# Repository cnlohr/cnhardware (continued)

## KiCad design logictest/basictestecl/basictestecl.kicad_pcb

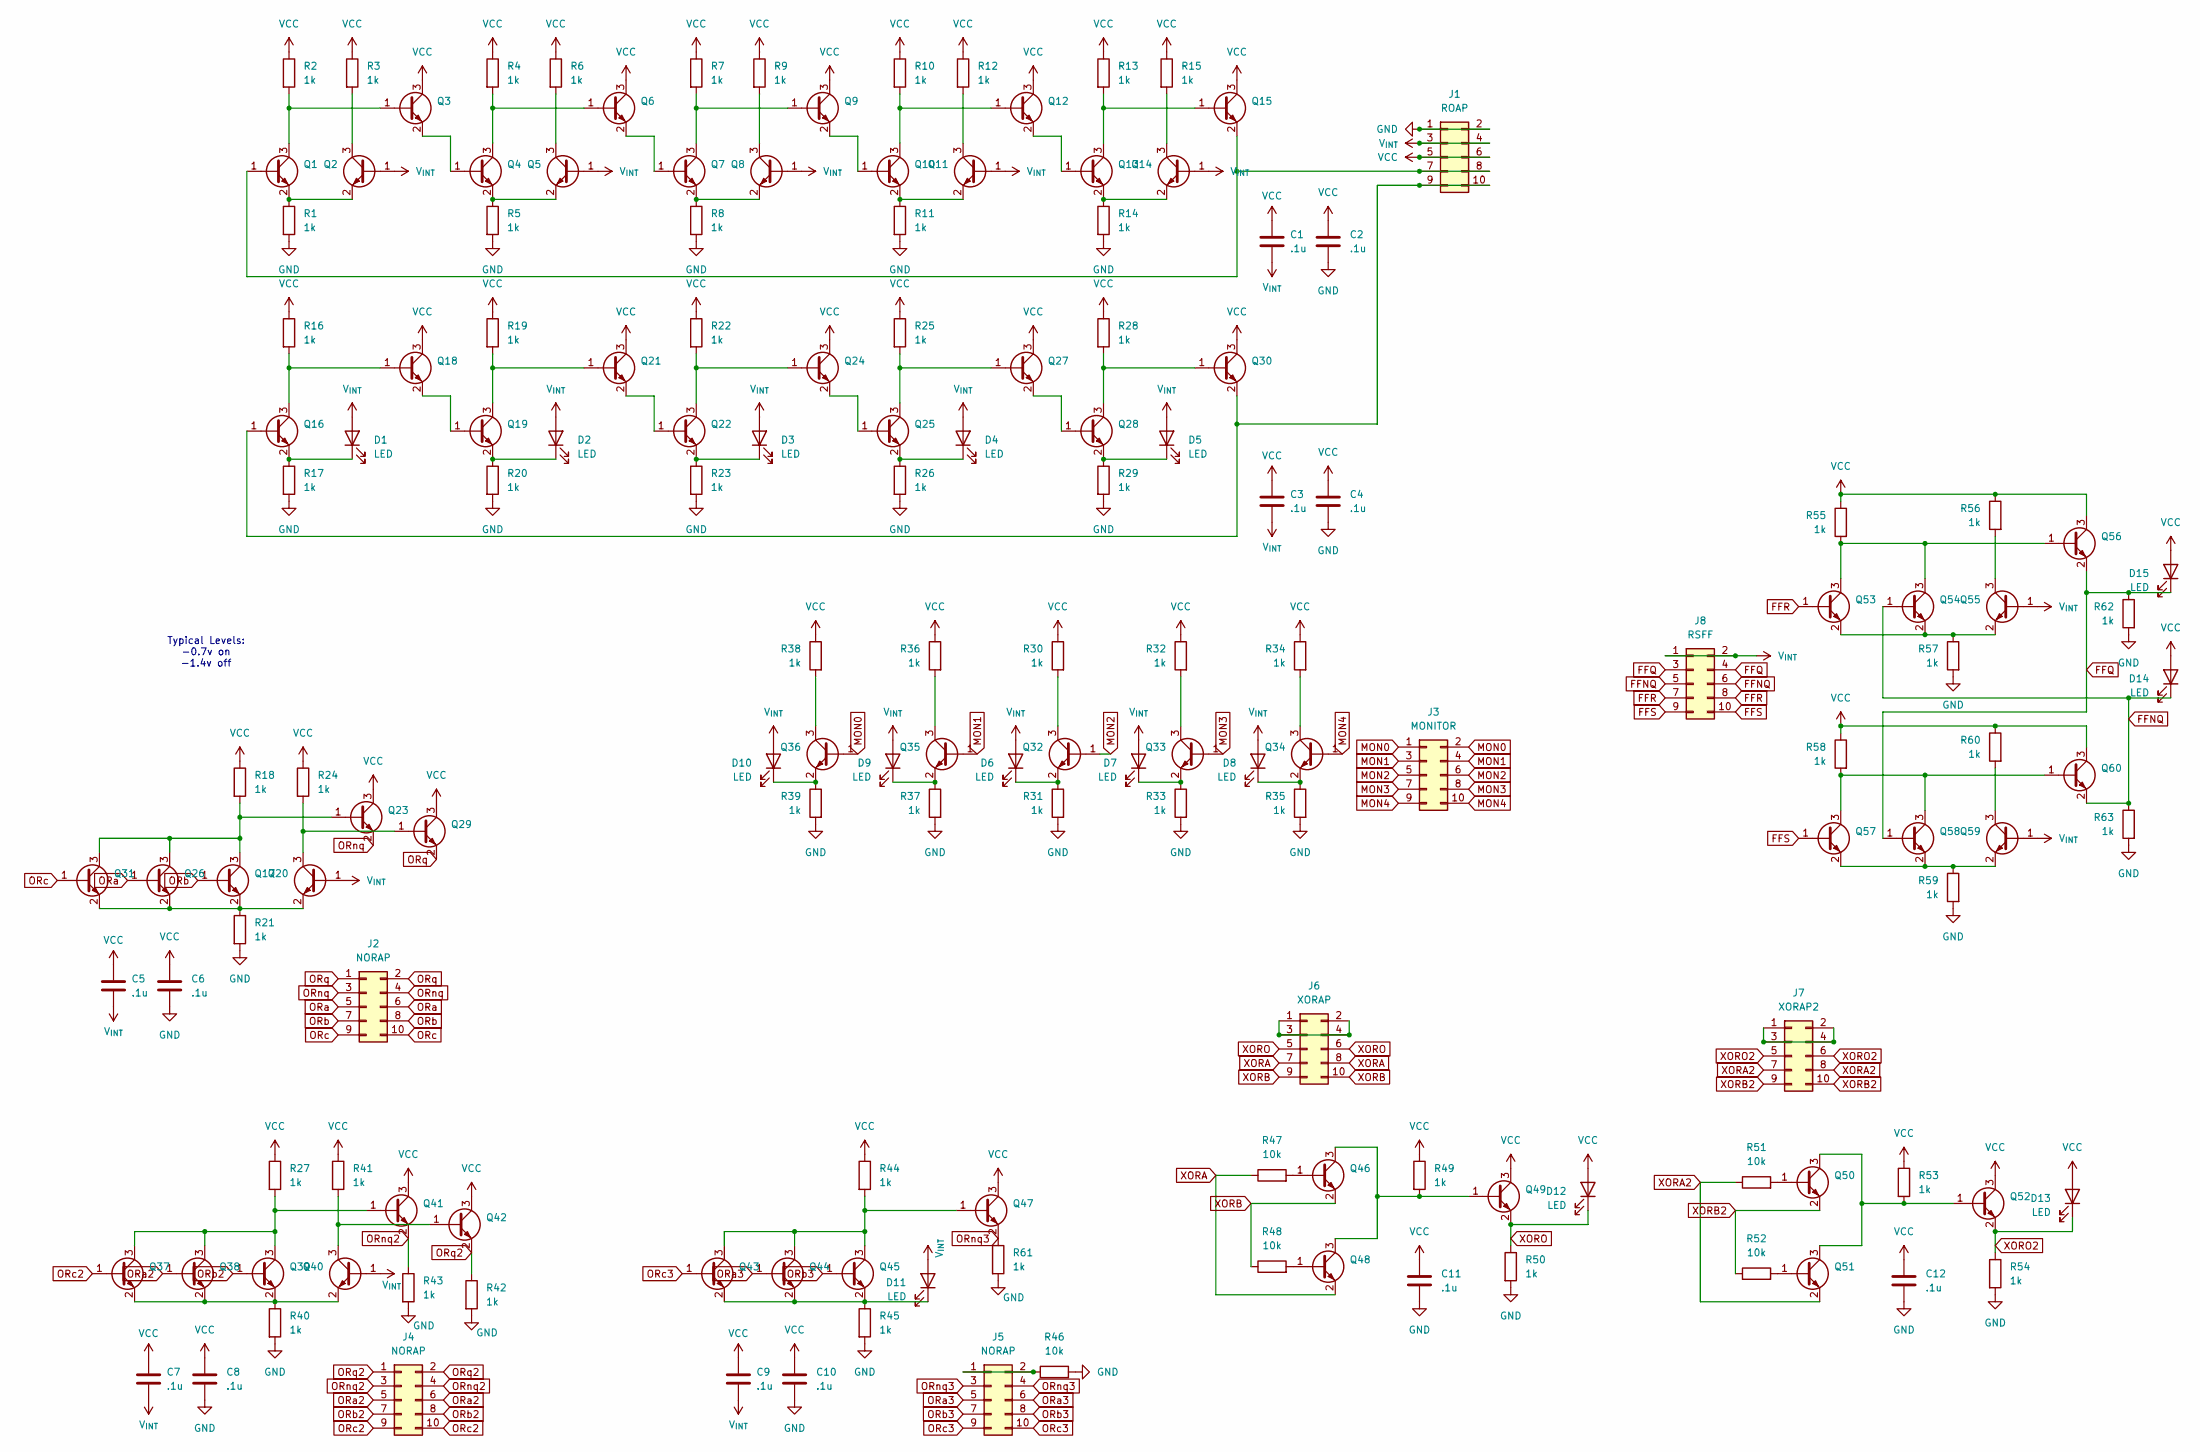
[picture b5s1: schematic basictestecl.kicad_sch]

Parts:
C1, C2, C3, C4, C5, C6, C7, C8, C9, C10, C11, C12: .1u; C_0402_1005Metric; LCSC C1525
D1, D2, D3, D4, D5, D6, D7, D8, D9, D10, D11, D12, D13, D14, D15: LED; LED_0402_1005Metric_COMPACT; LCSC C52675960
J1: ROAP; PinHeader_2x05_P2.54mm_Vertical; LCSC C53055680
J2, J4, J5: NORAP; PinHeader_2x05_P2.54mm_Vertical; LCSC C53055680
J3: MONITOR; PinHeader_2x05_P2.54mm_Vertical; LCSC C53055680
J6: XORAP; PinHeader_2x05_P2.54mm_Vertical; LCSC C53055680
J7: XORAP2; PinHeader_2x05_P2.54mm_Vertical; LCSC C53055680
J8: RSFF; PinHeader_2x05_P2.54mm_Vertical; LCSC C53055680
Q1, Q2, Q3, Q4, Q5, Q6, Q7, Q8, Q9, Q10, Q11, Q12, Q13, Q14, Q15, Q16, Q17, Q18, Q19, Q20, Q21, Q22, Q23, Q24, Q25, Q26, Q27, Q28, Q29, Q30, Q31, Q32, Q33, Q34, Q35, Q36, Q37, Q38, Q39, Q40, Q41, Q42, Q43, Q44, Q45, Q46, Q47, Q48, Q49, Q50, Q51, Q52, Q53, Q54, Q55, Q56, Q57, Q58, Q59, Q60: Q_NPN_BEC; DFN1006-3-NCH; LCSC C41355105
R1, R2, R3, R4, R5, R6, R7, R8, R9, R10, R11, R12, R13, R14, R15, R16, R17, R18, R19, R20, R21, R22, R23, R24, R25, R26, R27, R28, R29, R30, R31, R32, R33, R34, R35, R36, R37, R38, R39, R40, R41, R42, R43, R44, R45, R49, R50, R53, R54, R55, R56, R57, R58, R59, R60, R61, R62, R63: 1k; R_0402_1005Metric_COMPACT; LCSC C11702
R46, R47, R48, R51, R52: 10k; R_0402_1005Metric_COMPACT; LCSC C25744

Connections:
FFNQ: D14.1 (K), J8.5, J8.6, Q54.1 (B), Q60.2 (E), R63.1
FFQ: D15.1 (K), J8.3, J8.4, Q56.2 (E), Q58.1 (B), R62.1
FFR: J8.7, J8.8, Q53.1 (B)
FFS: J8.9, J8.10, Q57.1 (B)
GND: C2.2, C4.2, C6.2, C8.2, C10.2, C11.2, C12.2, J1.1, J1.2, R1.2, R5.2, R8.2, R11.2, R14.2, R17.2, R20.2, R21.2, R23.2, R26.2, R29.2, R31.2, R33.2, R35.2, R37.2, R39.2, R40.2, R42.2, R43.2, R45.2, R46.2, R50.2, R54.2, R57.2, R59.2, R61.2, R62.2, R63.2
MON0: J3.1, J3.2, Q36.1 (B)
MON1: J3.3, J3.4, Q35.1 (B)
MON2: J3.5, J3.6, Q32.1 (B)
MON3: J3.7, J3.8, Q33.1 (B)
MON4: J3.9, J3.10, Q34.1 (B)
unnamed: D1.1 (K), Q16.2 (E), R17.1
unnamed: D2.1 (K), Q19.2 (E), R20.1
unnamed: D3.1 (K), Q22.2 (E), R23.1
unnamed: D4.1 (K), Q25.2 (E), R26.1
unnamed: D5.1 (K), Q28.2 (E), R29.1
unnamed: D6.1 (K), Q32.2 (E), R31.1
unnamed: D7.1 (K), Q33.2 (E), R33.1
unnamed: D8.1 (K), Q34.2 (E), R35.1
unnamed: D9.1 (K), Q35.2 (E), R37.1
unnamed: D10.1 (K), Q36.2 (E), R39.1
unnamed: D11.1 (K), Q43.2 (E), Q44.2 (E), Q45.2 (E), R45.1
unnamed: J1.7, J1.8, Q1.1 (B), Q15.2 (E)
unnamed: J1.9, J1.10, Q16.1 (B), Q30.2 (E)
unnamed: J5.1, J5.2, R46.1
unnamed: J6.1, J6.2, J6.3, J6.4
unnamed: J7.1, J7.2, J7.3, J7.4
unnamed: Q1.3 (C), Q3.1 (B), R2.2
unnamed: Q1.2 (E), Q2.2 (E), R1.1
unnamed: Q2.3 (C), R3.2
unnamed: Q3.2 (E), Q4.1 (B)
unnamed: Q4.3 (C), Q6.1 (B), R4.2
unnamed: Q4.2 (E), Q5.2 (E), R5.1
unnamed: Q5.3 (C), R6.2
unnamed: Q6.2 (E), Q7.1 (B)
unnamed: Q7.3 (C), Q9.1 (B), R7.2
unnamed: Q7.2 (E), Q8.2 (E), R8.1
unnamed: Q8.3 (C), R9.2
unnamed: Q9.2 (E), Q10.1 (B)
unnamed: Q10.3 (C), Q12.1 (B), R10.2
unnamed: Q10.2 (E), Q11.2 (E), R11.1
unnamed: Q11.3 (C), R12.2
unnamed: Q12.2 (E), Q13.1 (B)
unnamed: Q13.3 (C), Q15.1 (B), R13.2
unnamed: Q13.2 (E), Q14.2 (E), R14.1
unnamed: Q14.3 (C), R15.2
unnamed: Q16.3 (C), Q18.1 (B), R16.2
unnamed: Q17.3 (C), Q23.1 (B), Q26.3 (C), Q31.3 (C), R18.2
unnamed: Q17.2 (E), Q20.2 (E), Q26.2 (E), Q31.2 (E), R21.1
unnamed: Q18.2 (E), Q19.1 (B)
unnamed: Q19.3 (C), Q21.1 (B), R19.2
unnamed: Q20.3 (C), Q29.1 (B), R24.2
unnamed: Q21.2 (E), Q22.1 (B)
unnamed: Q22.3 (C), Q24.1 (B), R22.2
unnamed: Q24.2 (E), Q25.1 (B)
unnamed: Q25.3 (C), Q27.1 (B), R25.2
unnamed: Q27.2 (E), Q28.1 (B)
unnamed: Q28.3 (C), Q30.1 (B), R28.2
unnamed: Q32.3 (C), R30.2
unnamed: Q33.3 (C), R32.2
unnamed: Q34.3 (C), R34.2
unnamed: Q35.3 (C), R36.2
unnamed: Q36.3 (C), R38.2
unnamed: Q37.3 (C), Q38.3 (C), Q39.3 (C), Q41.1 (B), R27.2
unnamed: Q37.2 (E), Q38.2 (E), Q39.2 (E), Q40.2 (E), R40.1
unnamed: Q40.3 (C), Q42.1 (B), R41.2
unnamed: Q43.3 (C), Q44.3 (C), Q45.3 (C), Q47.1 (B), R44.2
unnamed: Q46.1 (B), R47.2
unnamed: Q46.3 (C), Q48.3 (C), Q49.1 (B), R49.2
unnamed: Q48.1 (B), R48.2
unnamed: Q50.1 (B), R51.2
unnamed: Q50.3 (C), Q51.3 (C), Q52.1 (B), R53.2
unnamed: Q51.1 (B), R52.2
unnamed: Q53.3 (C), Q54.3 (C), Q56.1 (B), R55.2
unnamed: Q53.2 (E), Q54.2 (E), Q55.2 (E), R57.1
unnamed: Q55.3 (C), R56.2
unnamed: Q57.3 (C), Q58.3 (C), Q60.1 (B), R58.2
unnamed: Q57.2 (E), Q58.2 (E), Q59.2 (E), R59.1
unnamed: Q59.3 (C), R60.2
ORa: J2.5, J2.6, Q26.1 (B)
ORa2: J4.5, J4.6, Q38.1 (B)
ORa3: J5.5, J5.6, Q44.1 (B)
ORb: J2.7, J2.8, Q17.1 (B)
ORb2: J4.7, J4.8, Q39.1 (B)
ORb3: J5.7, J5.8, Q45.1 (B)
ORc: J2.9, J2.10, Q31.1 (B)
ORc2: J4.9, J4.10, Q37.1 (B)
ORc3: J5.9, J5.10, Q43.1 (B)
ORnq: J2.3, J2.4, Q23.2 (E)
ORnq2: J4.3, J4.4, Q41.2 (E), R43.1
ORnq3: J5.3, J5.4, Q47.2 (E), R61.1
ORq: J2.1, J2.2, Q29.2 (E)
ORq2: J4.1, J4.2, Q42.2 (E), R42.1
VCC: C1.2, C2.1, C3.2, C4.1, C5.2, C6.1, C7.2, C8.1, C9.2, C10.1, C11.1, C12.1, D12.2 (A), D13.2 (A), D14.2 (A), D15.2 (A), J1.5, J1.6, Q3.3 (C), Q6.3 (C), Q9.3 (C), Q12.3 (C), Q15.3 (C), Q18.3 (C), Q21.3 (C), Q23.3 (C), Q24.3 (C), Q27.3 (C), Q29.3 (C), Q30.3 (C), Q41.3 (C), Q42.3 (C), Q47.3 (C), Q49.3 (C), Q52.3 (C), Q56.3 (C), Q60.3 (C), R2.1, R3.1, R4.1, R6.1, R7.1, R9.1, R10.1, R12.1, R13.1, R15.1, R16.1, R18.1, R19.1, R22.1, R24.1, R25.1, R27.1, R28.1, R30.1, R32.1, R34.1, R36.1, R38.1, R41.1, R44.1, R49.1, R53.1, R55.1, R56.1, R58.1, R60.1
V_{INT}: C1.1, C3.1, C5.1, C7.1, C9.1, D1.2 (A), D2.2 (A), D3.2 (A), D4.2 (A), D5.2 (A), D6.2 (A), D7.2 (A), D8.2 (A), D9.2 (A), D10.2 (A), D11.2 (A), J1.3, J1.4, J8.1, J8.2, Q2.1 (B), Q5.1 (B), Q8.1 (B), Q11.1 (B), Q14.1 (B), Q20.1 (B), Q40.1 (B), Q55.1 (B), Q59.1 (B)
XORA: J6.7, J6.8, Q48.2 (E), R47.1
XORA2: J7.7, J7.8, Q51.2 (E), R51.1
XORB: J6.9, J6.10, Q46.2 (E), R48.1
XORB2: J7.9, J7.10, Q50.2 (E), R52.1
XORO: D12.1 (K), J6.5, J6.6, Q49.2 (E), R50.1
XORO2: D13.1 (K), J7.5, J7.6, Q52.2 (E), R54.1

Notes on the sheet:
Typical Levels: -0.7v on -1.4v off

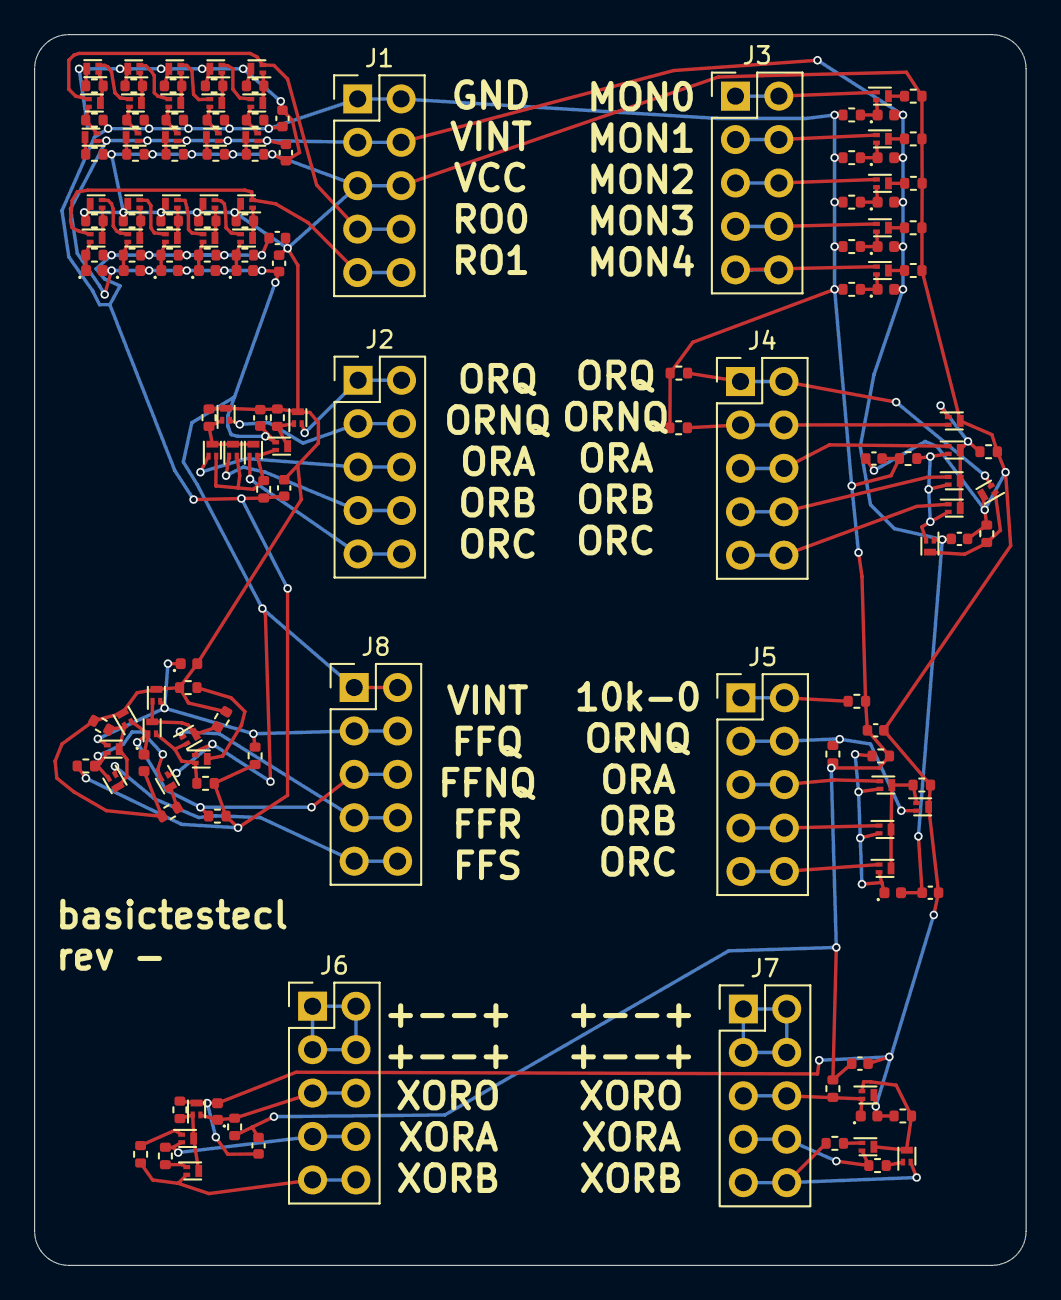
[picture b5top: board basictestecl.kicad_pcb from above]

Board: 2 copper layers, 58.0 x 72.0 mm, 158 parts (0 on the bottom side), 100 nets.

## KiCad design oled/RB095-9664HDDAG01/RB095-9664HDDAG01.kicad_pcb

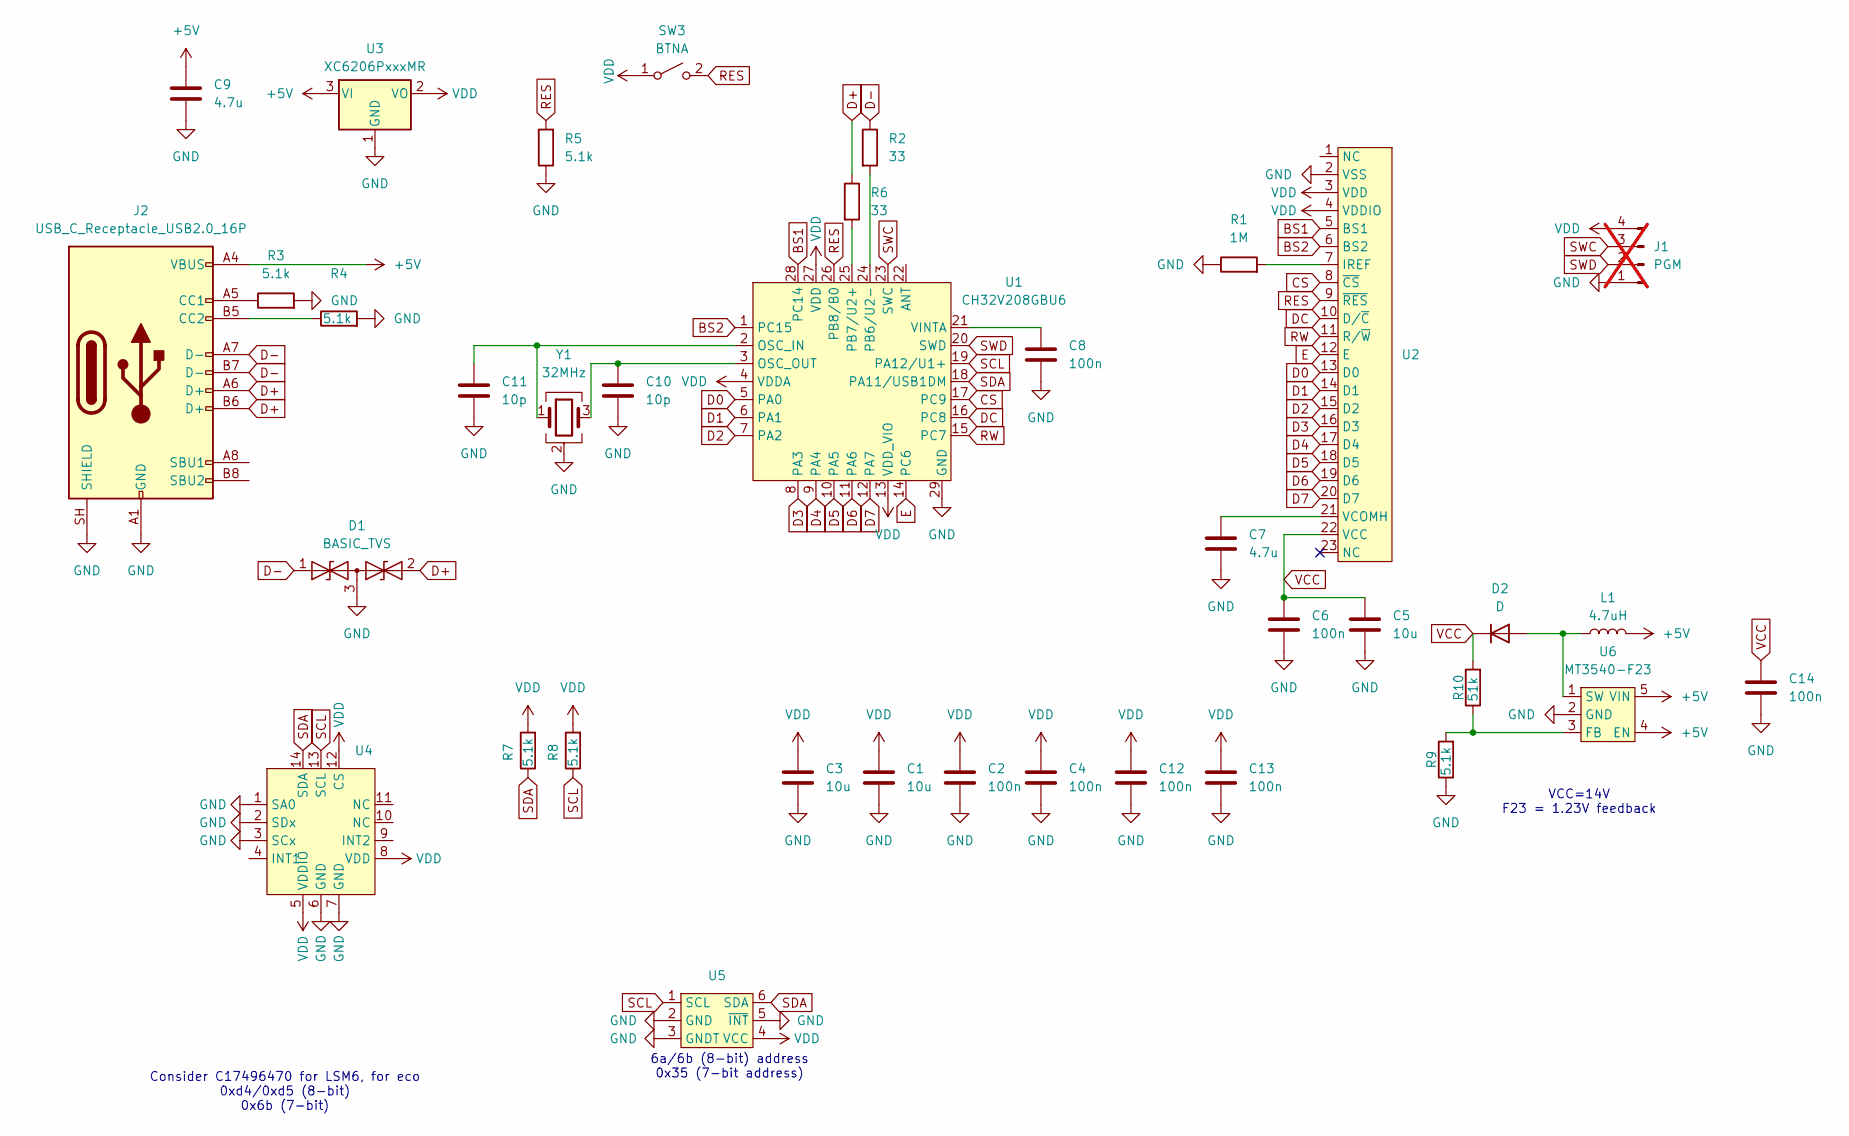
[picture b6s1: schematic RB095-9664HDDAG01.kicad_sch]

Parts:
C1, C3, C5: 10u; C_1206_3216Metric; LCSC C13585
C2, C4, C6, C8, C12, C13, C14: 100n; C_0402_1005Metric; LCSC C1525
C7, C9: 4.7u; C_1206_3216Metric; LCSC C29823
C10, C11: 10p; C_0402_1005Metric; LCSC C32949
D1: BASIC_TVS; SOT-23; LCSC C32677
D2: D; D_SOD-323; LCSC C191023
J1: PGM; PinHeader_1x04_P2.54mm_Vertical; not fitted
J2: USB_C_Receptacle_USB2.0_16P; USB_C_TIGHT_IN_BOARD_161N-4BC21665; LCSC C23376537
L1: 4.7uH; L_0805_2012Metric; LCSC C86088
R1: 1M; R_0402_1005Metric; LCSC C43675
R2, R6: 33; R_0402_1005Metric; LCSC C25105
R3, R4, R5, R7, R8, R9: 5.1k; R_0402_1005Metric; LCSC C25905
R10: 51k; R_0402_1005Metric; LCSC C25794
SW3: BTNA; TS-1187A-B-A-B-TACTILE; LCSC C42400804
U1: CH32V208GBU6; QFN-28-1EP_4x4mm_P0.4mm_EP2.3x2.3mm; LCSC C7434833
U2: RB095-9664HDDAG01_COLOR_OLED
U3: XC6206PxxxMR; SOT-23-3; LCSC C5446
U4: LGA-14_3x2.5mm_P0.5mm_LayoutBorder3x4y_EVEN_PADS; LCSC C41785564
U5: SOT-23-6; LCSC C3715882
U6: MT3540-F23; SOT-23-5; LCSC C181783
Y1: 32MHz; Crystal_SMD_2016-4Pin_2.0x1.6mm; LCSC C383840

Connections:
+5V: C9.1, J2.A4 (VBUS), J2.A9 (VBUS), J2.B4 (VBUS), J2.B9 (VBUS), L1.2, U3.3 (VI), U6.4 (EN), U6.5 (VIN)
BS1: U1.28 (PC14), U2.5 (BS1)
BS2: U1.1 (PC15), U2.6 (BS2)
CS: U1.17 (PC9), U2.8 (~CS)
D0: U1.5 (PA0), U2.13 (D0)
D1: U1.6 (PA1), U2.14 (D1)
D2: U1.7 (PA2), U2.15 (D2)
D3: U1.8 (PA3), U2.16 (D3)
D4: U1.9 (PA4), U2.17 (D4)
D5: U1.10 (PA5), U2.18 (D5)
D6: U1.11 (PA6), U2.19 (D6)
D7: U1.12 (PA7), U2.20 (D7)
D+: D1.2 (A2), J2.A6 (D+), J2.B6 (D+), R6.1
D-: D1.1 (A1), J2.A7 (D-), J2.B7 (D-), R2.1
DC: U1.16 (PC8), U2.10 (D/~C)
E: U1.14 (PC6), U2.12 (E)
GND: C1.2, C2.2, C3.2, C4.2, C5.2, C6.2, C7.2, C8.2, C9.2, C10.2, C11.2, C12.2, C13.2, C14.2, D1.3 (common), J1.1, J2.A1 (GND), J2.A12 (GND), J2.B1 (GND), J2.B12 (GND), J2.SH (SHIELD), R1.1, R3.2, R4.2, R5.1, R9.1, U1.29 (GND), U2.2 (VSS), U3.1 (GND), U4.1 (SA0), U4.2 (SDx), U4.3 (SCx), U4.6 (GND), U4.7 (GND), U5.2 (GND), U5.3 (GNDT), U5.5 (~INT), U6.2 (GND), Y1.2 (G), Y1.4 (G)
unnamed: D2.2 (A), L1.1, U6.1 (SW)
unnamed: J2.A5 (CC1), R3.1
unnamed: J2.B5 (CC2), R4.1
unnamed: C11.1, U1.2 (OSC_IN), Y1.1
unnamed: C10.1, U1.3 (OSC_OUT), Y1.3
unnamed: R2.2, U1.24 (PB6/U2-)
unnamed: R6.2, U1.25 (PB7/U2+)
unnamed: C8.1, U1.21 (VINTA)
unnamed: R1.2, U2.7 (IREF)
unnamed: C7.1, U2.21 (VCOMH)
unnamed: R9.2, R10.1, U6.3 (FB)
RES: R5.2, SW3.2 (B), U1.26 (PB8/B0), U2.9 (~RES)
RW: U1.15 (PC7), U2.11 (R/~W)
SCL: R8.1, U1.19 (PA12/U1+), U4.13 (SCL), U5.1 (SCL)
SDA: R7.1, U1.18 (PA11/USB1DM), U4.14 (SDA), U5.6 (SDA)
SWC: J1.3, U1.23 (SWC)
SWD: J1.2, U1.20 (SWD)
VCC: C5.1, C6.1, C14.1, D2.1 (K), R10.2, U2.22 (VCC)
VDD: C1.1, C2.1, C3.1, C4.1, C12.1, C13.1, J1.4, R7.2, R8.2, SW3.1 (A), U1.4 (VDDA), U1.13 (VDD_VIO), U1.27 (VDD), U2.3 (VDD), U2.4 (VDDIO), U3.2 (VO), U4.5 (VDDIO), U4.8 (VDD), U4.12 (CS), U5.4 (VCC)

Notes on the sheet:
VCC=14V F23 = 1.23V feedback
Consider C17496470 for LSM6, for eco 0xd4/0xd5 (8-bit) 0x6b (7-bit)
6a/6b (8-bit) address 0x35 (7-bit address)

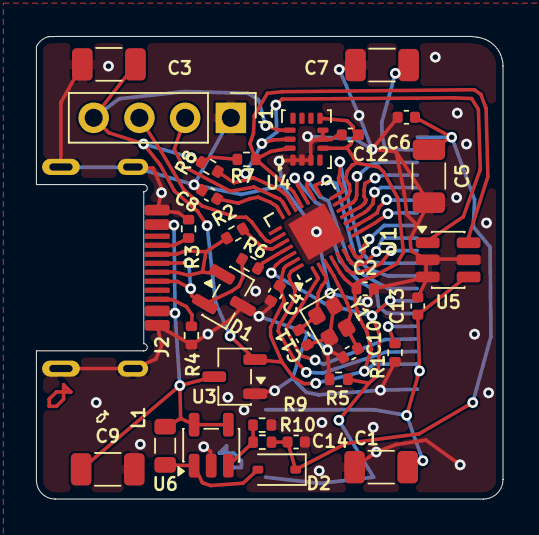
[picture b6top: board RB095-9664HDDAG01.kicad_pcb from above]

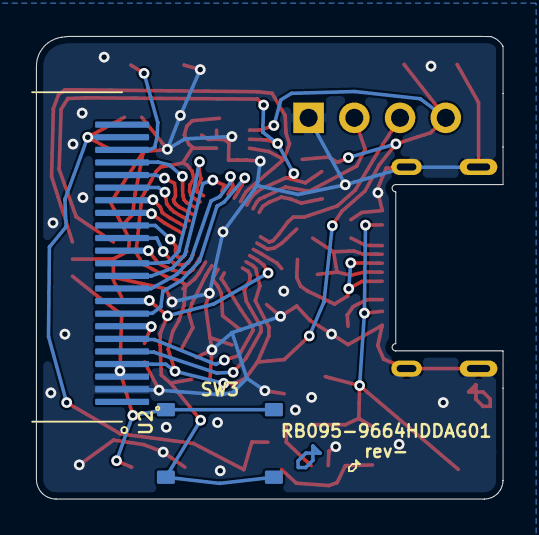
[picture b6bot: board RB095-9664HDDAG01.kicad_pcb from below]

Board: 2 copper layers, 25.9 x 25.7 mm, 37 parts (2 on the bottom side), 36 nets.

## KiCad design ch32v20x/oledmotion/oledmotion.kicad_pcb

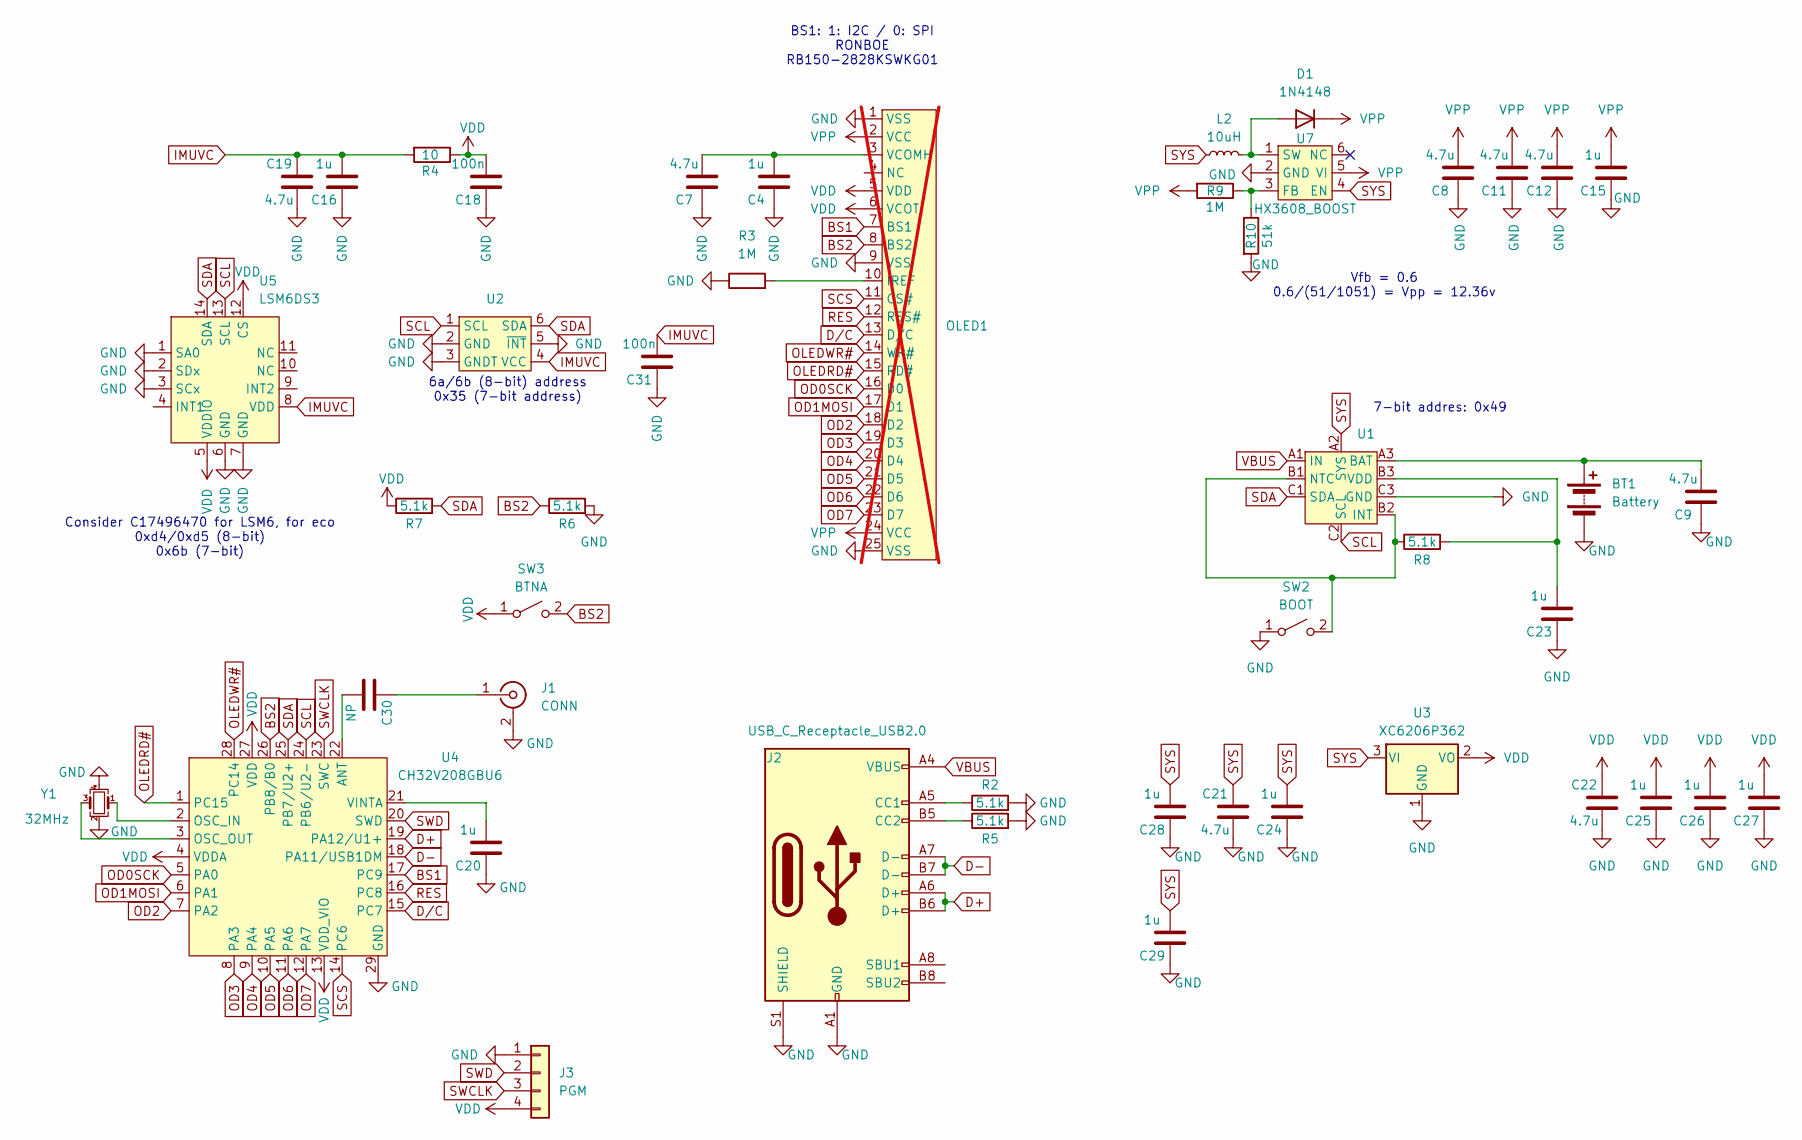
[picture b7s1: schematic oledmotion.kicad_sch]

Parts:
BT1: Battery; PinHeader_1x02_P2.54mm_Vertical
C4, C15, C16, C20, C23, C24, C25, C26, C27, C28, C29: 1u; R_0402_1005Metric; LCSC C52923
C7, C8, C9, C11, C12, C19, C21, C22: 4.7u; C_1206_3216Metric; LCSC C29823
C18, C31: 100n; R_0402_1005Metric; LCSC C307331
C30: NP; C_0603_1608Metric; LCSC NP
D1: 1N4148; D_SOD-323; LCSC C2128
J1: CONN; U.FL_Hirose_U.FL-R-SMT-1_Vertical
J2: USB_C_Receptacle_USB2.0; USB_C_TIGHT_IN_BOARD_161N-4BC21665; LCSC C23376537
J3: PGM; PinHeader_1x04_P2.54mm_Vertical
L2: 10uH; L_1008_2520Metric; LCSC C37428
OLED1: RB150-2828KSWKG01; not fitted
R2, R5, R7: 5.1k; R_0402_1005Metric; LCSC C105872
R3, R9: 1M; R_0402_1005Metric_COMPACT; LCSC C26083
R4: 10; R_0402_1005Metric_COMPACT; LCSC C25077
R6, R8: 5.1k; R_0402_1005Metric; LCSC C25905
R10: 51k; R_0402_1005Metric_COMPACT; LCSC C25794
SW2: BOOT; SW-SMD_TS2011C-411-03528; LCSC C42400804
SW3: BTNA; SW-SMD_TS2011C-411-03528; LCSC C42400804
U1: WLCSP-9-P0.5mm; LCSC C5125890
U2: SOT-23-6; LCSC C3715882
U3: XC6206P362; SOT-23; LCSC C50593818
U4: CH32V208GBU6; QFN-28-P0.4mm-2.8x2.8EP
U5: LSM6DS3; LGA-14_3x2.5mm_P0.5mm_LayoutBorder3x4y_EVEN_PADS; LCSC C784817
U7: HX3608_BOOST; SOT-23-6; LCSC C296278
Y1: 32MHz; Crystal_SMD_2016-4Pin_2.0x1.6mm; LCSC C37635323

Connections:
BS1: OLED1.7 (BS1), U4.17 (PC9)
BS2: OLED1.8 (BS2), R6.1, SW3.2 (B), U4.26 (PB8/B0)
D+: J2.A6 (D+), J2.B6 (D+), U4.19 (PA12/U1+)
D-: J2.A7 (D-), J2.B7 (D-), U4.18 (PA11/USB1DM)
D/C: OLED1.13 (D/C), U4.15 (PC7)
GND: BT1.2 (-), C4.2, C7.2, C8.2, C9.2, C11.2, C12.2, C15.2, C16.2, C18.2, C19.1, C20.2, C21.1, C22.1, C23.2, C24.2, C25.2, C26.2, C27.2, C28.2, C29.2, C31.2, J1.2 (Ext), J2.A1 (GND), J2.A12 (GND), J2.B1 (GND), J2.B12 (GND), J2.S1 (SHIELD), J3.1, OLED1.1 (VSS), OLED1.9 (VSS), OLED1.25 (VSS), R2.2, R3.1, R5.2, R6.2, R10.2, SW2.1 (A), U1.C3 (GND), U2.2 (GND), U2.3 (GNDT), U2.5 (~INT), U3.1 (GND), U4.29 (GND), U5.1 (SA0), U5.2 (SDx), U5.3 (SCx), U5.6 (GND), U5.7 (GND), U7.2 (GND), Y1.2, Y1.4
IMUVC: C16.1, C19.2, C31.1, R4.2, U2.4 (VCC), U5.8 (VDD)
unnamed: BT1.1 (+), C9.1, U1.A3 (BAT)
unnamed: D1.2 (A), L2.2, U7.1 (SW)
unnamed: C30.2, J1.1 (In)
unnamed: J2.A5 (CC1), R2.1
unnamed: J2.B5 (CC2), R5.1
unnamed: OLED1.10 (IREF), R3.2
unnamed: C4.1, C7.1, OLED1.3 (VCOMH)
unnamed: R8.1, SW2.2 (B), U1.B1 (NTC), U1.B2 (INT)
unnamed: C23.1, R8.2, U1.B3 (VDD)
unnamed: C30.1, U4.22 (ANT)
unnamed: U4.2 (OSC_IN), Y1.1
unnamed: U4.3 (OSC_OUT), Y1.3
unnamed: C20.1, U4.21 (VINTA)
unnamed: R9.1, R10.1, U7.3 (FB)
OD0SCK: OLED1.16 (D0), U4.5 (PA0)
OD1MOSI: OLED1.17 (D1), U4.6 (PA1)
OD2: OLED1.18 (D2), U4.7 (PA2)
OD3: OLED1.19 (D3), U4.8 (PA3)
OD4: OLED1.20 (D4), U4.9 (PA4)
OD5: OLED1.21 (D5), U4.10 (PA5)
OD6: OLED1.22 (D6), U4.11 (PA6)
OD7: OLED1.23 (D7), U4.12 (PA7)
OLEDRD#: OLED1.15 (RD#), U4.1 (PC15)
OLEDWR#: OLED1.14 (WR#), U4.28 (PC14)
RES: OLED1.12 (RES#), U4.16 (PC8)
SCL: U1.C2 (SCL), U2.1 (SCL), U4.24 (PB6/U2-), U5.13 (SCL)
SCS: OLED1.11 (CS#), U4.14 (PC6)
SDA: R7.2, U1.C1 (SDA), U2.6 (SDA), U4.25 (PB7/U2+), U5.14 (SDA)
SWCLK: J3.3, U4.23 (SWC)
SWD: J3.2, U4.20 (SWD)
SYS: C21.2, C24.1, C28.1, C29.1, L2.1, U1.A2 (SYS), U3.3 (VI), U7.4 (EN)
VBUS: J2.A4 (VBUS), J2.A9 (VBUS), J2.B4 (VBUS), J2.B9 (VBUS), U1.A1 (IN)
VDD: C18.1, C22.2, C25.1, C26.1, C27.1, J3.4, OLED1.5 (VDD), OLED1.6 (VCOT), R4.1, R7.1, SW3.1 (A), U3.2 (VO), U4.4 (VDDA), U4.13 (VDD_VIO), U4.27 (VDD), U5.5 (VDDIO), U5.12 (CS)
VPP: C8.1, C11.1, C12.1, C15.1, D1.1 (K), OLED1.2 (VCC), OLED1.24 (VCC), R9.2, U7.5 (VI)

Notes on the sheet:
Consider C17496470 for LSM6, for eco 0xd4/0xd5 (8-bit) 0x6b (7-bit)
7-bit addres: 0x49
BS1: 1: I2C / 0: SPI RONBOE RB150-2828KSWKG01
6a/6b (8-bit) address 0x35 (7-bit address)
Vfb = 0.6 0.6/(51/1051) = Vpp = 12.36v

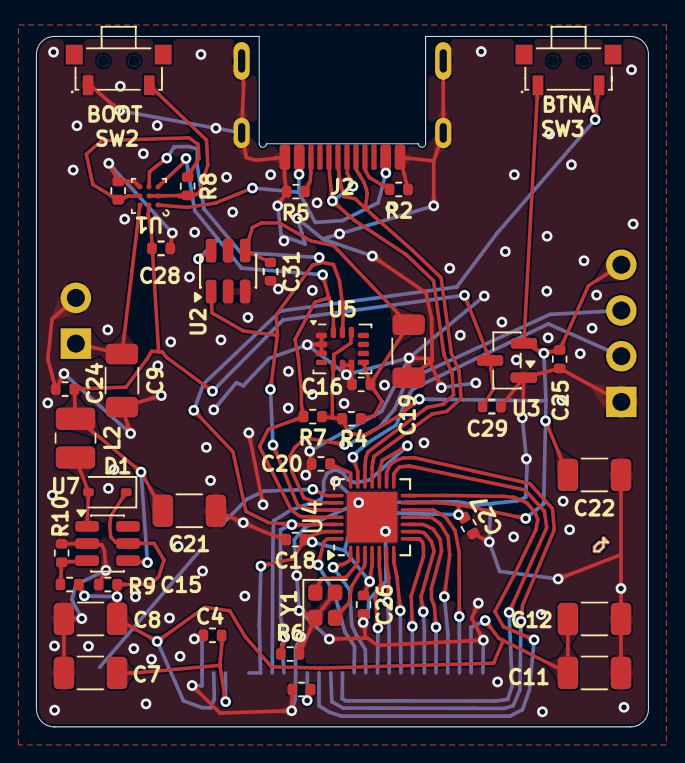
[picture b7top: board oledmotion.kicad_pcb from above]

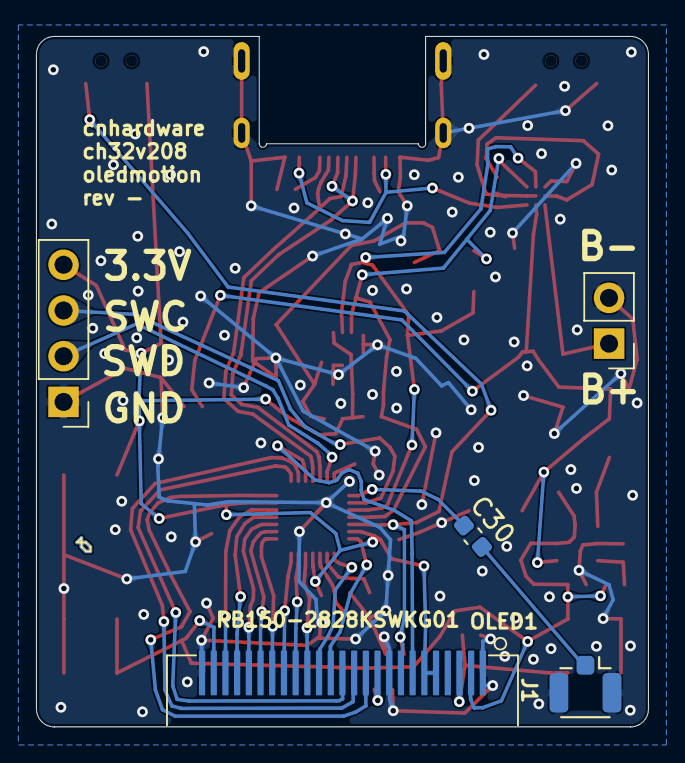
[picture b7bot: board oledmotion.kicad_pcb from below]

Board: 2 copper layers, 34.0 x 38.4 mm, 47 parts (5 on the bottom side), 41 nets.

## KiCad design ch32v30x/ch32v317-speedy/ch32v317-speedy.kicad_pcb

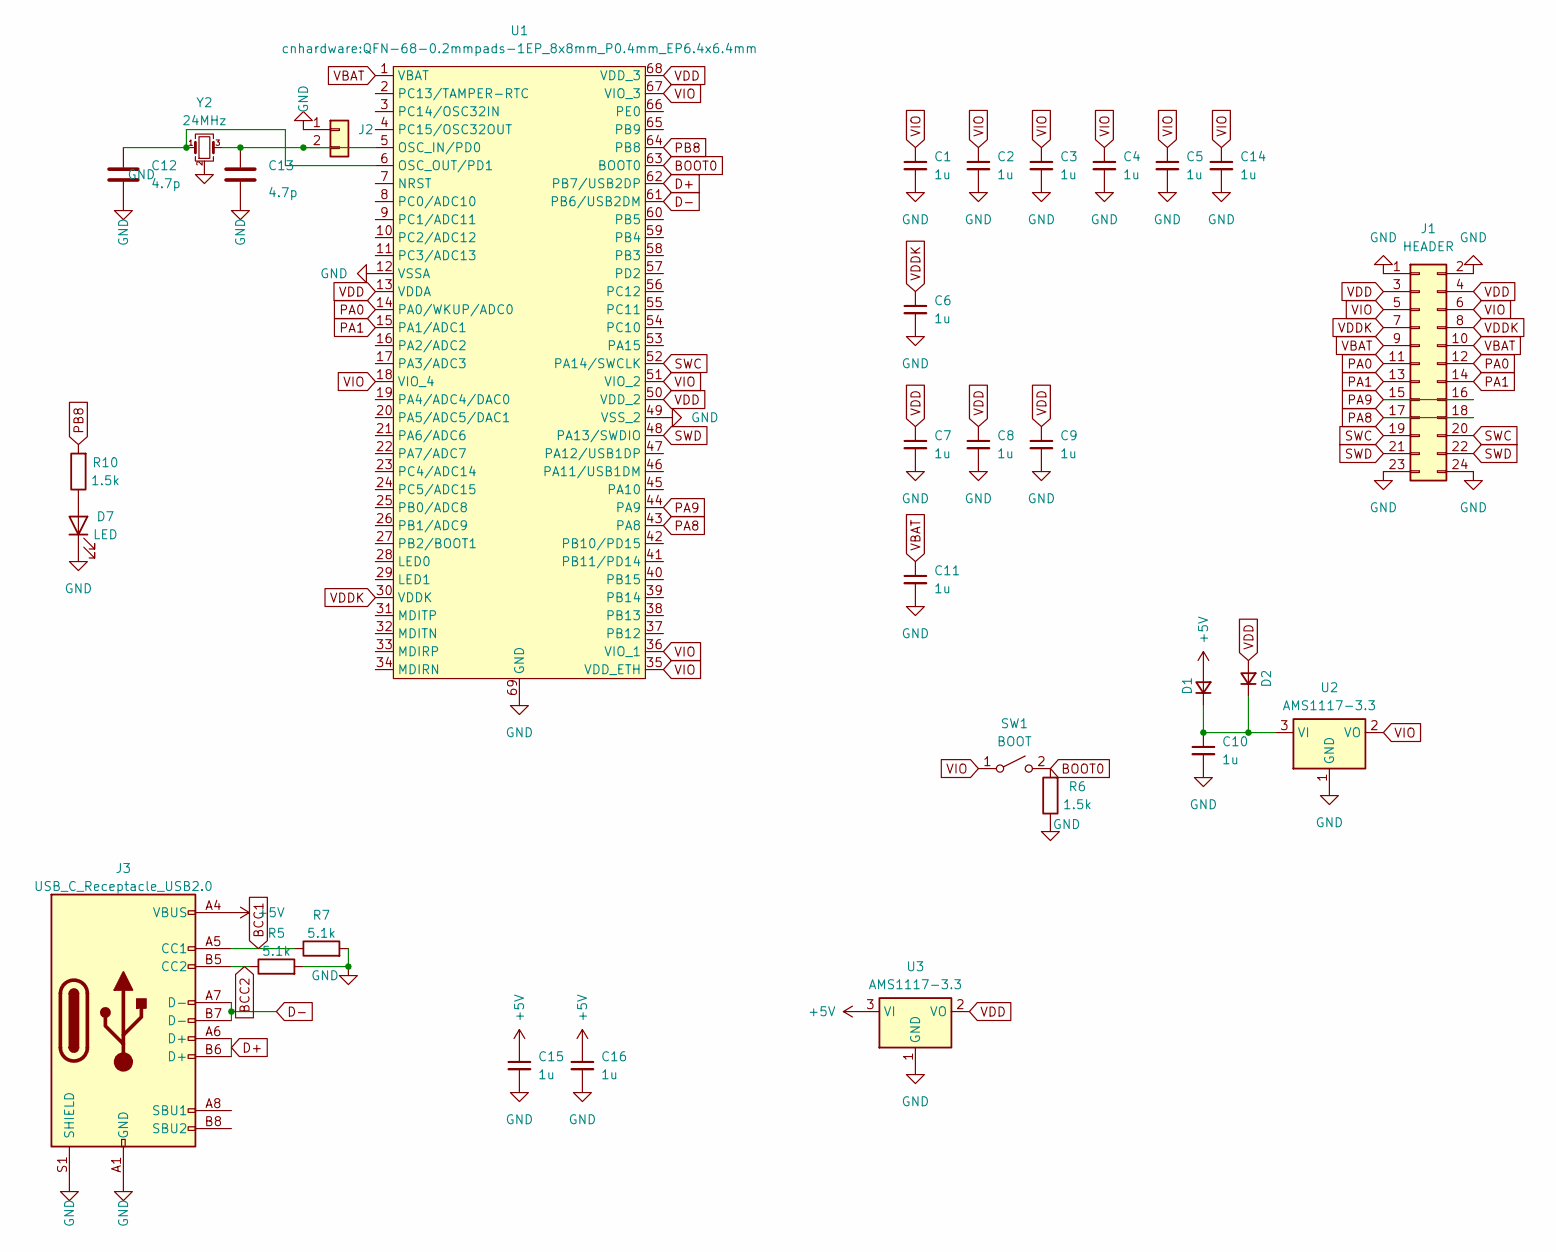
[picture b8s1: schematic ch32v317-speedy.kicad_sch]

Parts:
C1, C2, C3, C4, C5, C6, C7, C8, C9, C10, C11, C14, C15, C16: 1u; C_0402_1005Metric; LCSC C52923
C12, C13: 4.7p; C_0402_1005Metric; LCSC C325453
D1, D2: D_Small; D_SOD-323; LCSC C191023
D7: LED; LED_0402_1005Metric; LCSC C74342
J1: HEADER; PinHeader_2x12_P2.54mm_Vertical
J2: Conn_01x02; PinHeader_1x02_P2.54mm_Vertical
J3: USB_C_Receptacle_USB2.0; USB_C_MOD_Receptacle_HRO_TYPE-C-31-M-12; LCSC C2765186
R5, R7: 5.1k; R_0402_1005Metric; LCSC C25905
R6, R10: 1.5k; R_0402_1005Metric; LCSC C25867
SW1: BOOT; TS-1187A-B-A-B-TACTILE; LCSC C318884
U1: QFN-68-0.2mmpads-1EP_8x8mm_P0.4mm_EP6.4x6.4mm; LCSC C49188393
U2, U3: AMS1117-3.3; SOT-223-3_TabPin2; LCSC C6186
Y2: 24MHz; Crystal_SMD_2016-4Pin_2.0x1.6mm; LCSC C50202078

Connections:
+5V: C15.1, C16.1, D1.2 (A), J3.A4 (VBUS), J3.A9 (VBUS), J3.B4 (VBUS), J3.B9 (VBUS), U3.3 (VI)
BCC1: J3.A5 (CC1), R7.1
BCC2: J3.B5 (CC2), R5.1
BOOT0: R6.2, SW1.2 (B), U1.63 (BOOT0)
D+: J3.A6 (D+), J3.B6 (D+), U1.62 (PB7/USB2DP)
D-: J3.A7 (D-), J3.B7 (D-), U1.61 (PB6/USB2DM)
GND: C1.2, C2.2, C3.2, C4.2, C5.2, C6.2, C7.2, C8.2, C9.2, C10.2, C11.2, C12.2, C13.2, C14.2, C15.2, C16.2, D7.1 (K), J1.1, J1.2, J1.23, J1.24, J2.1, J3.A1 (GND), J3.A12 (GND), J3.B1 (GND), J3.B12 (GND), J3.S1 (SHIELD), R5.2, R6.1, R7.2, U1.12 (VSSA), U1.49 (VSS_2), U1.69 (GND), U2.1 (GND), U3.1 (GND), Y2.2 (G), Y2.4 (G)
unnamed: C10.1, D1.1 (K), D2.1 (K), U2.3 (VI)
unnamed: D7.2 (A), R10.1
unnamed: C13.1, J2.2, U1.5 (OSC_IN/PD0), Y2.3
unnamed: C12.1, U1.6 (OSC_OUT/PD1), Y2.1
PA0: J1.11, J1.12, U1.14 (PA0/WKUP/ADC0)
PA1: J1.13, J1.14, U1.15 (PA1/ADC1)
PA8: J1.17, J1.18, U1.43 (PA8)
PA9: J1.15, J1.16, U1.44 (PA9)
PB8: R10.2, U1.64 (PB8)
SWC: J1.19, J1.20, U1.52 (PA14/SWCLK)
SWD: J1.21, J1.22, U1.48 (PA13/SWDIO)
VBAT: C11.1, J1.9, J1.10, U1.1 (VBAT)
VDD: C7.1, C8.1, C9.1, D2.2 (A), J1.3, J1.4, U1.13 (VDDA), U1.50 (VDD_2), U1.68 (VDD_3), U3.2 (VO)
VDDK: C6.1, J1.7, J1.8, U1.30 (VDDK)
VIO: C1.1, C2.1, C3.1, C4.1, C5.1, C14.1, J1.5, J1.6, SW1.1 (A), U1.18 (VIO_4), U1.35 (VDD_ETH), U1.36 (VIO_1), U1.51 (VIO_2), U1.67 (VIO_3), U2.2 (VO)

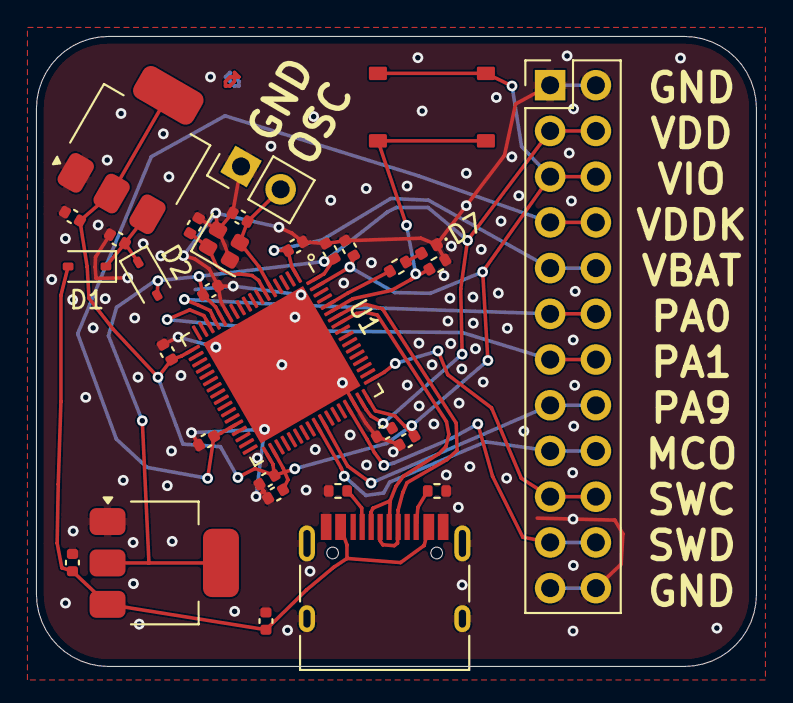
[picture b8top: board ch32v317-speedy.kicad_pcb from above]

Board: 2 copper layers, 40.0 x 35.0 mm, 31 parts (0 on the bottom side), 22 nets.
